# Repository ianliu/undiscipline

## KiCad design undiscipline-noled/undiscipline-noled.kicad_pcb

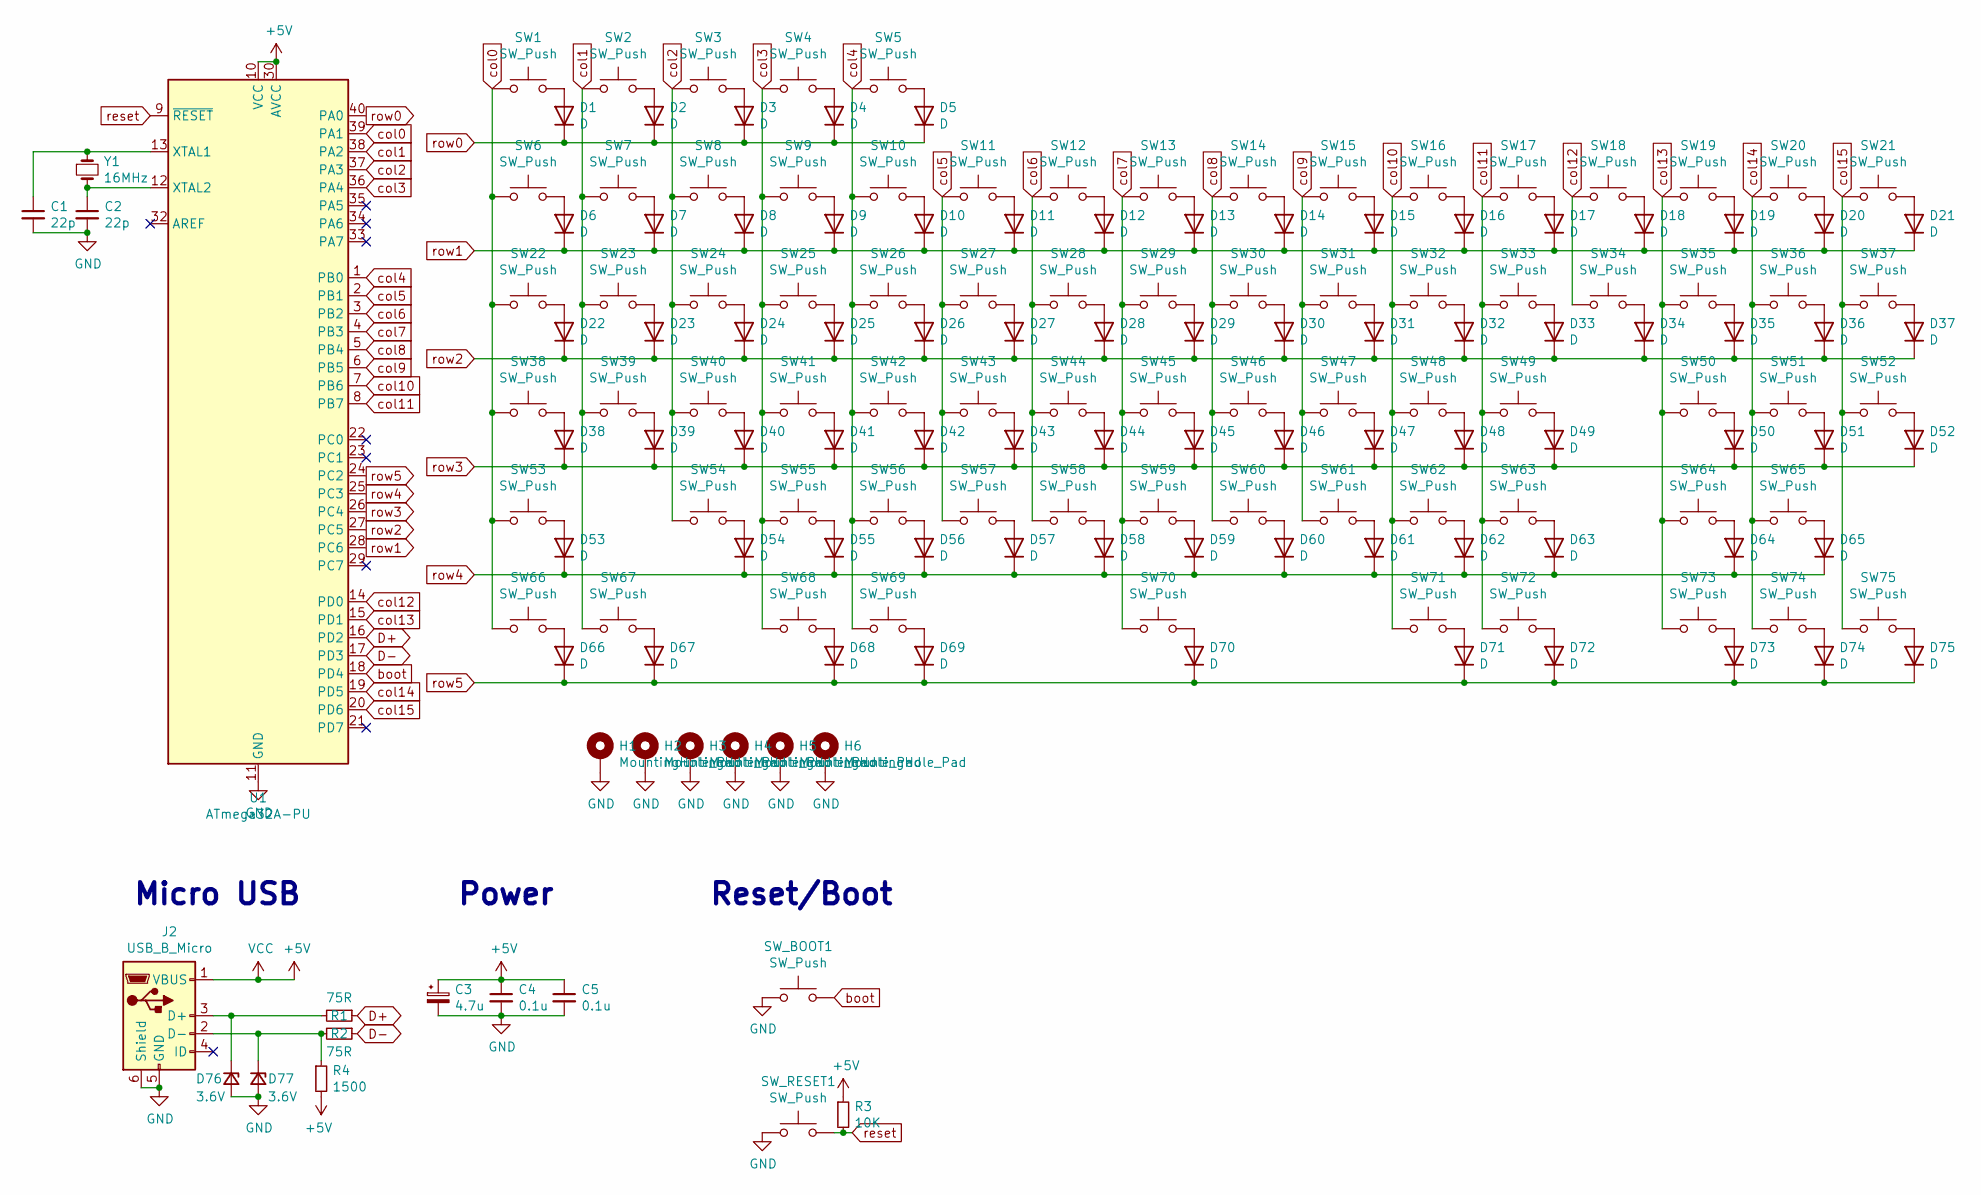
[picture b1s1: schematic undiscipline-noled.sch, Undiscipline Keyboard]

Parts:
C1, C2: 22p; C_Disc_D3.8mm_W2.6mm_P2.50mm
C3: 4.7u; CP_Radial_D5.0mm_P2.50mm
C4, C5: 0.1u; C_Disc_D4.3mm_W1.9mm_P5.00mm
D1, D2, D3, D4, D5, D6, D7, D8, D9, D10, D11, D12, D13, D14, D15, D16, D17, D18, D19, D20, D21, D22, D23, D24, D25, D26, D27, D28, D29, D30, D31, D32, D33, D34, D35, D36, D37, D38, D39, D40, D41, D42, D43, D44, D45, D46, D47, D48, D49, D50, D51, D52, D53, D54, D55, D56, D57, D58, D59, D60, D61, D62, D63, D64, D65, D66, D67, D68, D69, D70, D71, D72, D73, D74, D75: D; D_T-1_P5.08mm_Horizontal
D76, D77: 3.6V; D_T-1_P5.08mm_Horizontal
H1, H2, H3, H4, H5, H6: MountingHole_Pad; MountingHole_2.2mm_M2_DIN965_Pad_TopBottom
J2: USB_B_Micro; MicroUSB
R1, R2: 75R; R_Axial_DIN0204_L3.6mm_D1.6mm_P5.08mm_Horizontal
R3: 10K; R_Axial_DIN0204_L3.6mm_D1.6mm_P5.08mm_Horizontal
R4: 1500; R_Axial_DIN0204_L3.6mm_D1.6mm_P5.08mm_Horizontal
SW1, SW2, SW3, SW4, SW5, SW6, SW7, SW8, SW9, SW10, SW11, SW12, SW13, SW14, SW15, SW16, SW17, SW18, SW20, SW21, SW23, SW24, SW25, SW26, SW27, SW28, SW29, SW30, SW31, SW32, SW33, SW34, SW36, SW37, SW39, SW40, SW41, SW42, SW43, SW44, SW45, SW46, SW47, SW48, SW49, SW51, SW52, SW53, SW54, SW55, SW56, SW57, SW58, SW59, SW60, SW61, SW62, SW63, SW65, SW73, SW74, SW75: SW_Push; SW_Cherry_MX_1.00u_Plate
SW19: SW_Push; SW_Cherry_MX_2.00u_Plate
SW22, SW35: SW_Push; SW_Cherry_MX_1.50u_Plate
SW38: SW_Push; SW_Cherry_MX_1.75u_Plate
SW50: SW_Push; SW_Cherry_MX_2.25u_Plate
SW64: SW_Push; SW_Cherry_MX_2.75u_Plate
SW66, SW67, SW68, SW69, SW71, SW72: SW_Push; SW_Cherry_MX_1.25u_Plate
SW70: SW_Push; SW_Cherry_MX_6.25u_Plate
SW_BOOT1: SW_Push; SW_PUSH_6mm
SW_RESET1: SW_Push; SW_PUSH_6mm
U1: ATmega32A-PU; DIP-40_W15.24mm
Y1: 16MHz; Crystal_HC49-4H_Vertical

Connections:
+5V: C3.1, C4.1, C5.1, J2.1 (VBUS), R3.1, R4.2, U1.10 (VCC), U1.30 (AVCC)
D+: R1.1, U1.16 (PD2)
D-: R2.1, U1.17 (PD3)
GND: C1.2, C2.2, C3.2, C4.2, C5.2, D76.2 (A), D77.2 (A), H1.1, H2.1, H3.1, H4.1, H5.1, H6.1, J2.5 (GND), J2.6 (Shield), SW_BOOT1.1, SW_RESET1.1, U1.11 (GND), U1.31 (GND)
unnamed: C1.1, U1.13 (XTAL1), Y1.1
unnamed: C2.1, U1.12 (XTAL2), Y1.2
unnamed: D1.2 (A), SW1.2
unnamed: D2.2 (A), SW2.2
unnamed: D3.2 (A), SW3.2
unnamed: D4.2 (A), SW4.2
unnamed: D5.2 (A), SW5.2
unnamed: D6.2 (A), SW6.2
unnamed: D7.2 (A), SW7.2
unnamed: D8.2 (A), SW8.2
unnamed: D9.2 (A), SW9.2
unnamed: D10.2 (A), SW10.2
unnamed: D11.2 (A), SW11.2
unnamed: D12.2 (A), SW12.2
unnamed: D13.2 (A), SW13.2
unnamed: D14.2 (A), SW14.2
unnamed: D15.2 (A), SW15.2
unnamed: D16.2 (A), SW16.2
unnamed: D17.2 (A), SW17.2
unnamed: D18.2 (A), SW18.2
unnamed: D19.2 (A), SW19.2
unnamed: D20.2 (A), SW20.2
unnamed: D21.2 (A), SW21.2
unnamed: D22.2 (A), SW22.2
unnamed: D23.2 (A), SW23.2
unnamed: D24.2 (A), SW24.2
unnamed: D25.2 (A), SW25.2
unnamed: D26.2 (A), SW26.2
unnamed: D27.2 (A), SW27.2
unnamed: D28.2 (A), SW28.2
unnamed: D29.2 (A), SW29.2
unnamed: D30.2 (A), SW30.2
unnamed: D31.2 (A), SW31.2
unnamed: D32.2 (A), SW32.2
unnamed: D33.2 (A), SW33.2
unnamed: D34.2 (A), SW34.2
unnamed: D35.2 (A), SW35.2
unnamed: D36.2 (A), SW36.2
unnamed: D37.2 (A), SW37.2
unnamed: D38.2 (A), SW38.2
unnamed: D39.2 (A), SW39.2
unnamed: D40.2 (A), SW40.2
unnamed: D41.2 (A), SW41.2
unnamed: D42.2 (A), SW42.2
unnamed: D43.2 (A), SW43.2
unnamed: D44.2 (A), SW44.2
unnamed: D45.2 (A), SW45.2
unnamed: D46.2 (A), SW46.2
unnamed: D47.2 (A), SW47.2
unnamed: D48.2 (A), SW48.2
unnamed: D49.2 (A), SW49.2
unnamed: D50.2 (A), SW50.2
unnamed: D51.2 (A), SW51.2
unnamed: D52.2 (A), SW52.2
unnamed: D53.2 (A), SW53.2
unnamed: D54.2 (A), SW54.2
unnamed: D55.2 (A), SW55.2
unnamed: D56.2 (A), SW56.2
unnamed: D57.2 (A), SW57.2
unnamed: D58.2 (A), SW58.2
unnamed: D59.2 (A), SW59.2
unnamed: D60.2 (A), SW60.2
unnamed: D61.2 (A), SW61.2
unnamed: D62.2 (A), SW62.2
unnamed: D63.2 (A), SW63.2
unnamed: D64.2 (A), SW64.2
unnamed: D65.2 (A), SW65.2
unnamed: D66.2 (A), SW66.2
unnamed: D67.2 (A), SW67.2
unnamed: D68.2 (A), SW68.2
unnamed: D69.2 (A), SW69.2
unnamed: D70.2 (A), SW70.2
unnamed: D71.2 (A), SW71.2
unnamed: D72.2 (A), SW72.2
unnamed: D73.2 (A), SW73.2
unnamed: D74.2 (A), SW74.2
unnamed: D75.2 (A), SW75.2
unnamed: D76.1 (K), J2.3 (D+), R1.2
unnamed: D77.1 (K), J2.2 (D-), R2.2, R4.1
boot: SW_BOOT1.2, U1.18 (PD4)
col0: SW1.1, SW6.1, SW22.1, SW38.1, SW53.1, SW66.1, U1.39 (PA1)
col1: SW2.1, SW7.1, SW23.1, SW39.1, SW67.1, U1.38 (PA2)
col2: SW3.1, SW8.1, SW24.1, SW40.1, SW54.1, U1.37 (PA3)
col3: SW4.1, SW9.1, SW25.1, SW41.1, SW55.1, SW68.1, U1.36 (PA4)
col4: SW5.1, SW10.1, SW26.1, SW42.1, SW56.1, SW69.1, U1.1 (PB0)
col5: SW11.1, SW27.1, SW43.1, SW57.1, U1.2 (PB1)
col6: SW12.1, SW28.1, SW44.1, SW58.1, U1.3 (PB2)
col7: SW13.1, SW29.1, SW45.1, SW59.1, SW70.1, U1.4 (PB3)
col8: SW14.1, SW30.1, SW46.1, SW60.1, U1.5 (PB4)
col9: SW15.1, SW31.1, SW47.1, SW61.1, U1.6 (PB5)
col10: SW16.1, SW32.1, SW48.1, SW62.1, SW71.1, U1.7 (PB6)
col11: SW17.1, SW33.1, SW49.1, SW63.1, SW72.1, U1.8 (PB7)
col12: SW18.1, SW34.1, U1.14 (PD0)
col13: SW19.1, SW35.1, SW50.1, SW64.1, SW73.1, U1.15 (PD1)
col14: SW20.1, SW36.1, SW51.1, SW65.1, SW74.1, U1.19 (PD5)
col15: SW21.1, SW37.1, SW52.1, SW75.1, U1.20 (PD6)
reset: R3.2, SW_RESET1.2, U1.9 (~RESET)
row0: D1.1 (K), D2.1 (K), D3.1 (K), D4.1 (K), D5.1 (K), U1.40 (PA0)
row1: D6.1 (K), D7.1 (K), D8.1 (K), D9.1 (K), D10.1 (K), D11.1 (K), D12.1 (K), D13.1 (K), D14.1 (K), D15.1 (K), D16.1 (K), D17.1 (K), D18.1 (K), D19.1 (K), D20.1 (K), D21.1 (K), U1.28 (PC6)
row2: D22.1 (K), D23.1 (K), D24.1 (K), D25.1 (K), D26.1 (K), D27.1 (K), D28.1 (K), D29.1 (K), D30.1 (K), D31.1 (K), D32.1 (K), D33.1 (K), D34.1 (K), D35.1 (K), D36.1 (K), D37.1 (K), U1.27 (PC5)
row3: D38.1 (K), D39.1 (K), D40.1 (K), D41.1 (K), D42.1 (K), D43.1 (K), D44.1 (K), D45.1 (K), D46.1 (K), D47.1 (K), D48.1 (K), D49.1 (K), D50.1 (K), D51.1 (K), D52.1 (K), U1.26 (PC4)
row4: D53.1 (K), D54.1 (K), D55.1 (K), D56.1 (K), D57.1 (K), D58.1 (K), D59.1 (K), D60.1 (K), D61.1 (K), D62.1 (K), D63.1 (K), D64.1 (K), D65.1 (K), U1.25 (PC3)
row5: D66.1 (K), D67.1 (K), D68.1 (K), D69.1 (K), D70.1 (K), D71.1 (K), D72.1 (K), D73.1 (K), D74.1 (K), D75.1 (K), U1.24 (PC2)

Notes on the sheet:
Micro USB
Power
Reset/Boot

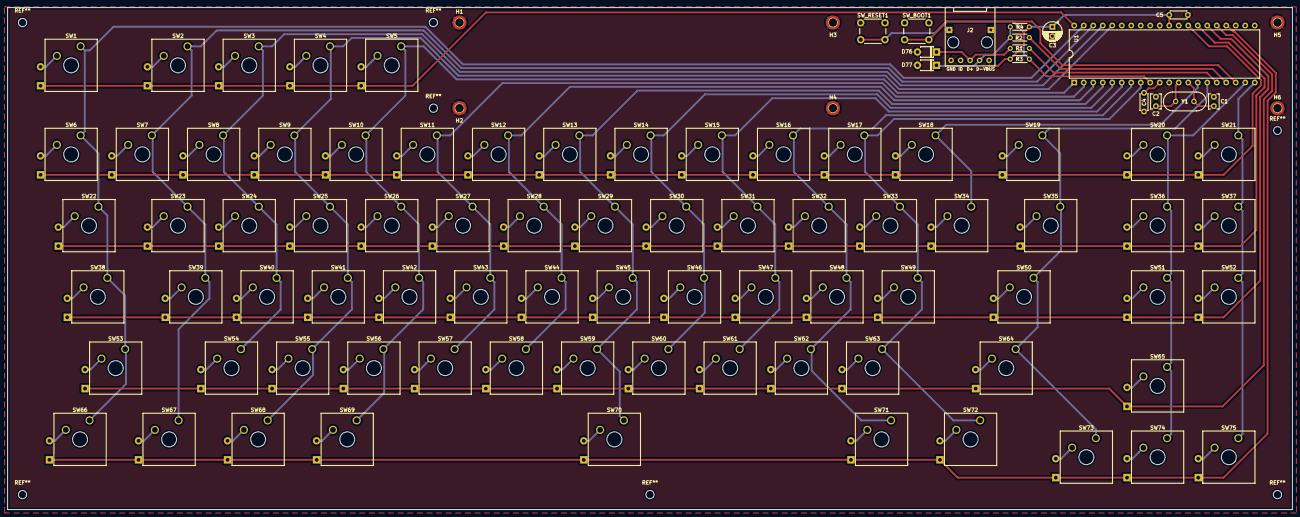
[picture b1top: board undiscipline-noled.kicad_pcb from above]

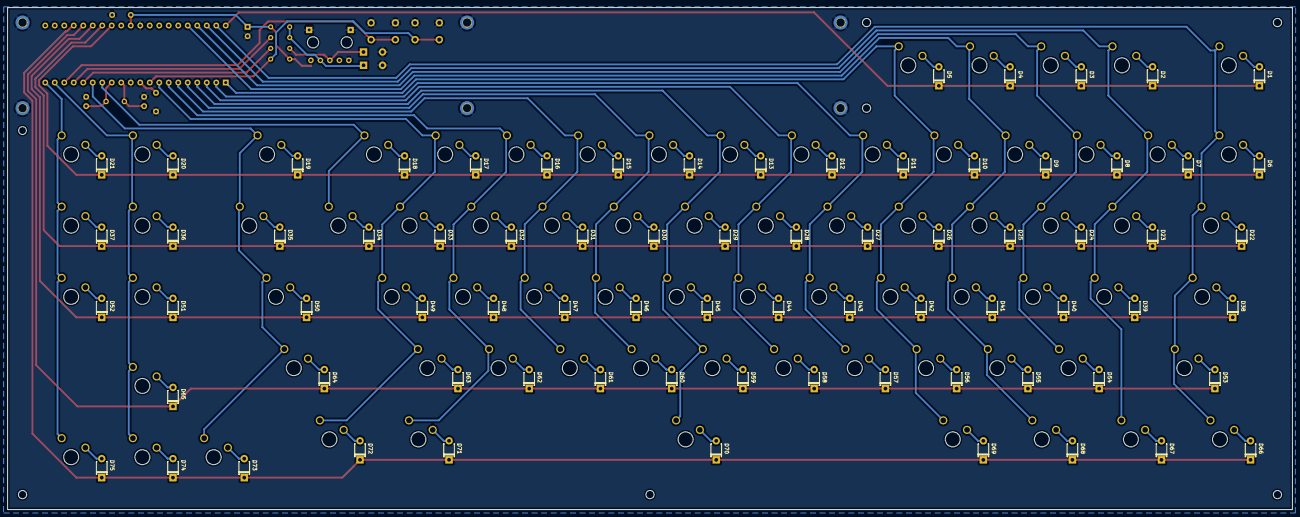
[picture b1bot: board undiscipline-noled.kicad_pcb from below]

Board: 4 copper layers, 343.6 x 134.2 mm, 172 parts (75 on the bottom side), 107 nets.

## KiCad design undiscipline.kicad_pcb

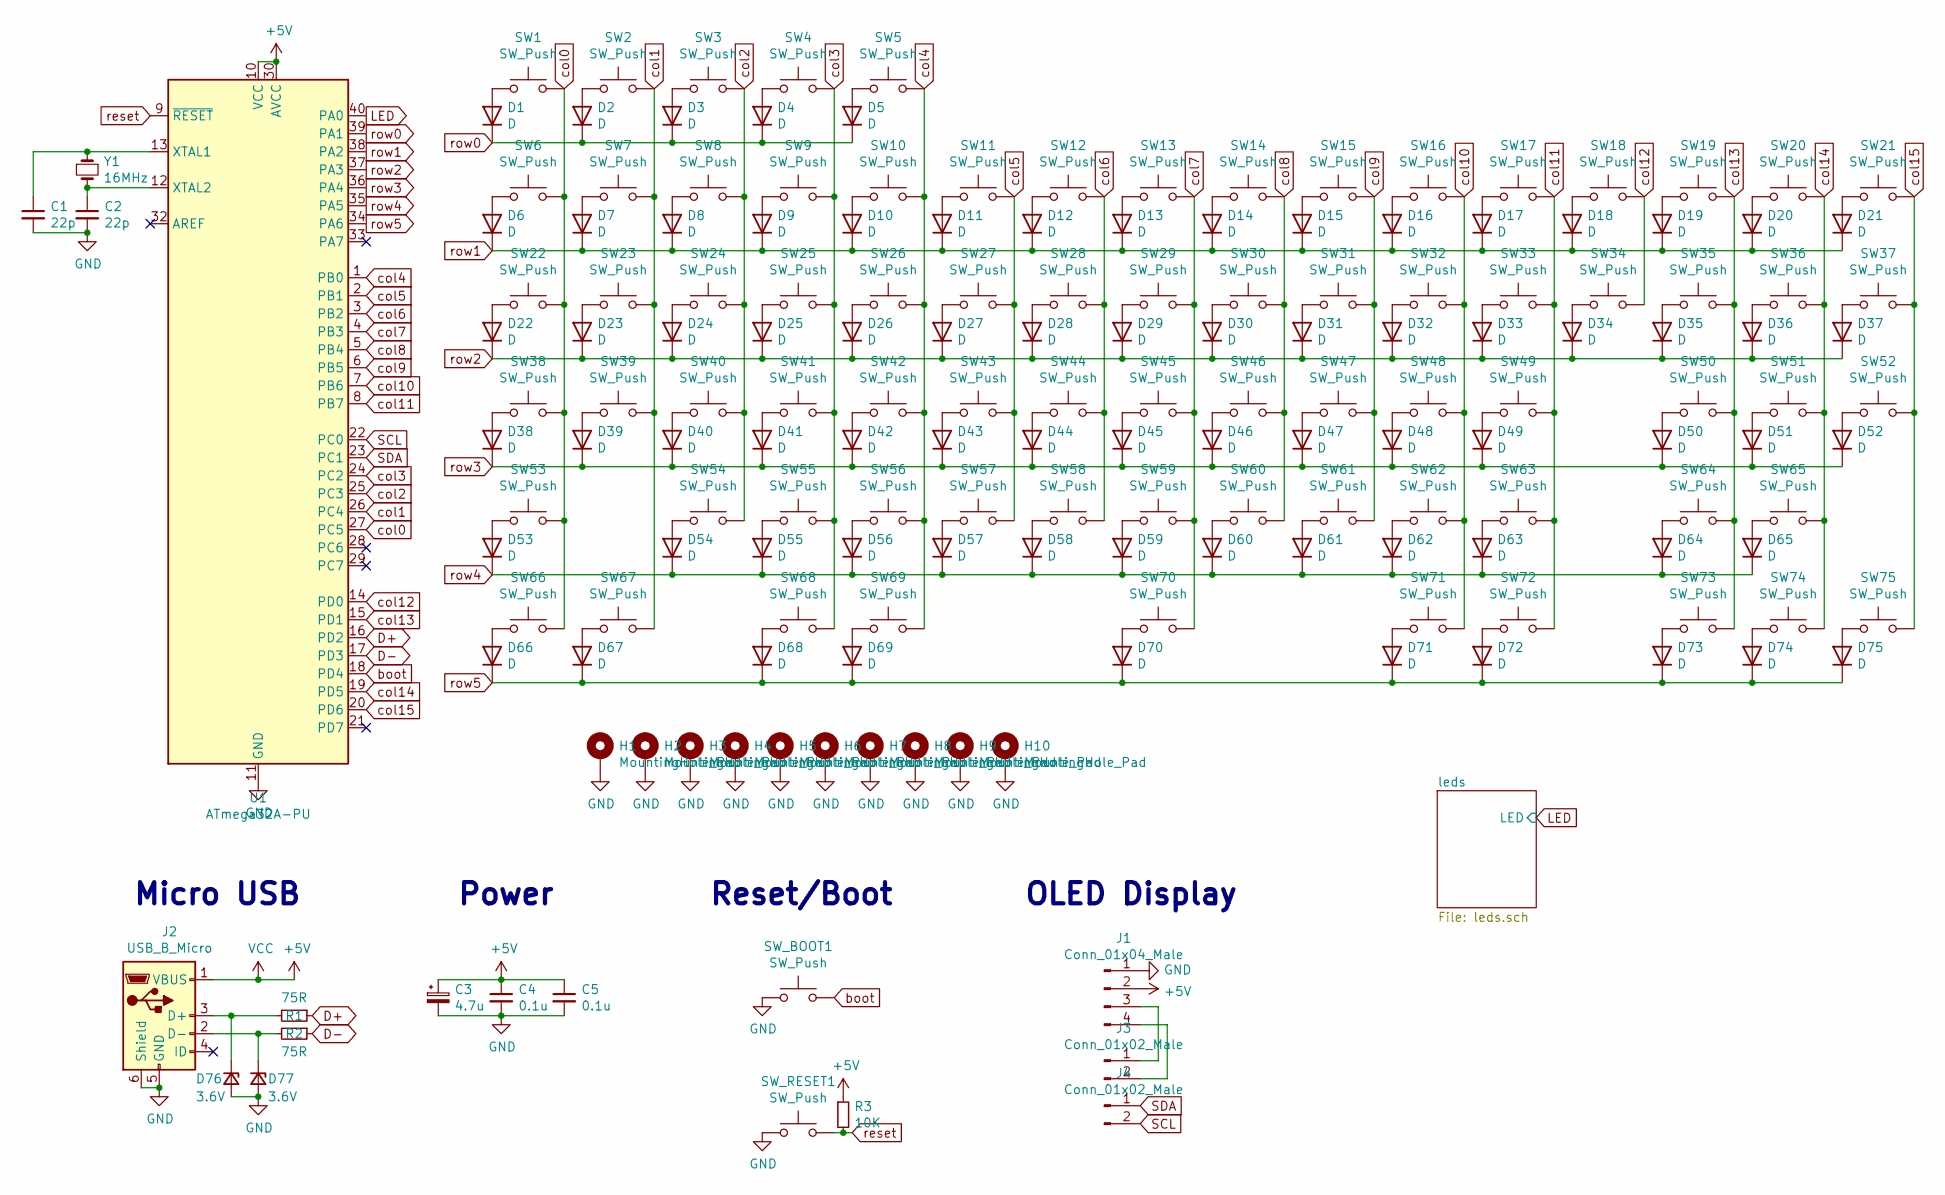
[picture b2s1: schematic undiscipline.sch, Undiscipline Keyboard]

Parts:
C1, C2: 22p; C_Disc_D3.8mm_W2.6mm_P2.50mm
C3: 4.7u; CP_Radial_D5.0mm_P2.50mm
C4, C5: 0.1u; C_Disc_D4.3mm_W1.9mm_P5.00mm
D1, D2, D3, D4, D5, D6, D7, D8, D9, D10, D11, D12, D13, D14, D15, D16, D17, D18, D19, D20, D21, D22, D23, D24, D25, D26, D27, D28, D29, D30, D31, D32, D33, D34, D35, D36, D37, D38, D39, D40, D41, D42, D43, D44, D45, D46, D47, D48, D49, D50, D51, D52, D53, D54, D55, D56, D57, D58, D59, D60, D61, D62, D63, D64, D65, D66, D67, D68, D69, D70, D71, D72, D73, D74, D75: D; D_T-1_P5.08mm_Horizontal
D76, D77: 3.6V; D_T-1_P5.08mm_Horizontal
H1, H2, H3, H4, H5, H6, H7, H8, H9, H10: MountingHole_Pad; MountingHole_2.2mm_M2_DIN965_Pad_TopBottom
J1: Conn_01x04_Male; OLED128x64
J2: USB_B_Micro; MicroUSB
J3, J4: Conn_01x02_Male; PinHeader_1x02_P2.54mm_Horizontal
R1, R2: 75R; R_Axial_DIN0204_L3.6mm_D1.6mm_P5.08mm_Horizontal
R3: 10K; R_Axial_DIN0204_L3.6mm_D1.6mm_P5.08mm_Horizontal
SW1, SW2, SW3, SW4, SW5, SW6, SW7, SW8, SW9, SW10, SW11, SW12, SW13, SW14, SW15, SW16, SW17, SW18, SW19, SW20, SW21, SW22, SW23, SW24, SW25, SW26, SW27, SW28, SW29, SW30, SW31, SW32, SW33, SW34, SW35, SW36, SW37, SW38, SW39, SW40, SW41, SW42, SW43, SW44, SW45, SW46, SW47, SW48, SW49, SW50, SW51, SW52, SW53, SW54, SW55, SW56, SW57, SW58, SW59, SW60, SW61, SW62, SW63, SW64, SW65, SW66, SW67, SW68, SW69, SW70, SW71, SW72, SW73, SW74, SW75: SW_Push; CherryMX_Kailh_Socket
SW_BOOT1: SW_Push; SW_PUSH_6mm
SW_RESET1: SW_Push; SW_PUSH_6mm
U1: ATmega32A-PU; DIP-40_W15.24mm
Y1: 16MHz; Crystal_HC49-4H_Vertical

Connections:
+5V: C3.1, C4.1, C5.1, J1.2, J2.1 (VBUS), R3.1, U1.10 (VCC), U1.30 (AVCC); also elsewhere on the board
D+: R1.1, U1.16 (PD2)
D-: R2.1, U1.17 (PD3)
GND: C1.2, C2.2, C3.2, C4.2, C5.2, D76.2 (A), D77.2 (A), H1.1, H2.1, H3.1, H4.1, H5.1, H6.1, H7.1, H8.1, H9.1, H10.1, J1.1, J2.5 (GND), J2.6 (Shield), SW_BOOT1.1, SW_RESET1.1, U1.11 (GND), U1.31 (GND); also elsewhere on the board
LED: U1.40 (PA0); also elsewhere on the board
unnamed: C1.1, U1.13 (XTAL1), Y1.1
unnamed: C2.1, U1.12 (XTAL2), Y1.2
unnamed: D1.2 (A), SW1.1
unnamed: D2.2 (A), SW2.1
unnamed: D3.2 (A), SW3.1
unnamed: D4.2 (A), SW4.1
unnamed: D5.2 (A), SW5.1
unnamed: D6.2 (A), SW6.1
unnamed: D7.2 (A), SW7.1
unnamed: D8.2 (A), SW8.1
unnamed: D9.2 (A), SW9.1
unnamed: D10.2 (A), SW10.1
unnamed: D11.2 (A), SW11.1
unnamed: D12.2 (A), SW12.1
unnamed: D13.2 (A), SW13.1
unnamed: D14.2 (A), SW14.1
unnamed: D15.2 (A), SW15.1
unnamed: D16.2 (A), SW16.1
unnamed: D17.2 (A), SW17.1
unnamed: D18.2 (A), SW18.1
unnamed: D19.2 (A), SW19.1
unnamed: D20.2 (A), SW20.1
unnamed: D21.2 (A), SW21.1
unnamed: D22.2 (A), SW22.1
unnamed: D23.2 (A), SW23.1
unnamed: D24.2 (A), SW24.1
unnamed: D25.2 (A), SW25.1
unnamed: D26.2 (A), SW26.1
unnamed: D27.2 (A), SW27.1
unnamed: D28.2 (A), SW28.1
unnamed: D29.2 (A), SW29.1
unnamed: D30.2 (A), SW30.1
unnamed: D31.2 (A), SW31.1
unnamed: D32.2 (A), SW32.1
unnamed: D33.2 (A), SW33.1
unnamed: D34.2 (A), SW34.1
unnamed: D35.2 (A), SW35.1
unnamed: D36.2 (A), SW36.1
unnamed: D37.2 (A), SW37.1
unnamed: D38.2 (A), SW38.1
unnamed: D39.2 (A), SW39.1
unnamed: D40.2 (A), SW40.1
unnamed: D41.2 (A), SW41.1
unnamed: D42.2 (A), SW42.1
unnamed: D43.2 (A), SW43.1
unnamed: D44.2 (A), SW44.1
unnamed: D45.2 (A), SW45.1
unnamed: D46.2 (A), SW46.1
unnamed: D47.2 (A), SW47.1
unnamed: D48.2 (A), SW48.1
unnamed: D49.2 (A), SW49.1
unnamed: D50.2 (A), SW50.1
unnamed: D51.2 (A), SW51.1
unnamed: D52.2 (A), SW52.1
unnamed: D53.2 (A), SW53.1
unnamed: D54.2 (A), SW54.1
unnamed: D55.2 (A), SW55.1
unnamed: D56.2 (A), SW56.1
unnamed: D57.2 (A), SW57.1
unnamed: D58.2 (A), SW58.1
unnamed: D59.2 (A), SW59.1
unnamed: D60.2 (A), SW60.1
unnamed: D61.2 (A), SW61.1
unnamed: D62.2 (A), SW62.1
unnamed: D63.2 (A), SW63.1
unnamed: D64.2 (A), SW64.1
unnamed: D65.2 (A), SW65.1
unnamed: D66.2 (A), SW66.1
unnamed: D67.2 (A), SW67.1
unnamed: D68.2 (A), SW68.1
unnamed: D69.2 (A), SW69.1
unnamed: D70.2 (A), SW70.1
unnamed: D71.2 (A), SW71.1
unnamed: D72.2 (A), SW72.1
unnamed: D73.2 (A), SW73.1
unnamed: D74.2 (A), SW74.1
unnamed: D75.2 (A), SW75.1
unnamed: D76.1 (K), J2.3 (D+), R1.2
unnamed 83: D77.1 (K), J2.2 (D-), R2.2; also elsewhere on the board
unnamed: J1.3, J3.1
unnamed: J1.4, J3.2
SCL: J4.2, U1.22 (PC0)
SDA: J4.1, U1.23 (PC1)
boot: SW_BOOT1.2, U1.18 (PD4)
col0: SW1.2, SW6.2, SW22.2, SW38.2, SW53.2, SW66.2, U1.27 (PC5)
col1: SW2.2, SW7.2, SW23.2, SW39.2, SW67.2, U1.26 (PC4)
col2: SW3.2, SW8.2, SW24.2, SW40.2, SW54.2, U1.25 (PC3)
col3: SW4.2, SW9.2, SW25.2, SW41.2, SW55.2, SW68.2, U1.24 (PC2)
col4: SW5.2, SW10.2, SW26.2, SW42.2, SW56.2, SW69.2, U1.1 (PB0)
col5: SW11.2, SW27.2, SW43.2, SW57.2, U1.2 (PB1)
col6: SW12.2, SW28.2, SW44.2, SW58.2, U1.3 (PB2)
col7: SW13.2, SW29.2, SW45.2, SW59.2, SW70.2, U1.4 (PB3)
col8: SW14.2, SW30.2, SW46.2, SW60.2, U1.5 (PB4)
col9: SW15.2, SW31.2, SW47.2, SW61.2, U1.6 (PB5)
col10: SW16.2, SW32.2, SW48.2, SW62.2, SW71.2, U1.7 (PB6)
col11: SW17.2, SW33.2, SW49.2, SW63.2, SW72.2, U1.8 (PB7)
col12: SW18.2, SW34.2, U1.14 (PD0)
col13: SW19.2, SW35.2, SW50.2, SW64.2, SW73.2, U1.15 (PD1)
col14: SW20.2, SW36.2, SW51.2, SW65.2, SW74.2, U1.19 (PD5)
col15: SW21.2, SW37.2, SW52.2, SW75.2, U1.20 (PD6)
reset: R3.2, SW_RESET1.2, U1.9 (~RESET)
row0: D1.1 (K), D2.1 (K), D3.1 (K), D4.1 (K), D5.1 (K), U1.39 (PA1)
row1: D6.1 (K), D7.1 (K), D8.1 (K), D9.1 (K), D10.1 (K), D11.1 (K), D12.1 (K), D13.1 (K), D14.1 (K), D15.1 (K), D16.1 (K), D17.1 (K), D18.1 (K), D19.1 (K), D20.1 (K), D21.1 (K), U1.38 (PA2)
row2: D22.1 (K), D23.1 (K), D24.1 (K), D25.1 (K), D26.1 (K), D27.1 (K), D28.1 (K), D29.1 (K), D30.1 (K), D31.1 (K), D32.1 (K), D33.1 (K), D34.1 (K), D35.1 (K), D36.1 (K), D37.1 (K), U1.37 (PA3)
row3: D38.1 (K), D39.1 (K), D40.1 (K), D41.1 (K), D42.1 (K), D43.1 (K), D44.1 (K), D45.1 (K), D46.1 (K), D47.1 (K), D48.1 (K), D49.1 (K), D50.1 (K), D51.1 (K), D52.1 (K), U1.36 (PA4)
row4: D53.1 (K), D54.1 (K), D55.1 (K), D56.1 (K), D57.1 (K), D58.1 (K), D59.1 (K), D60.1 (K), D61.1 (K), D62.1 (K), D63.1 (K), D64.1 (K), D65.1 (K), U1.35 (PA5)
row5: D66.1 (K), D67.1 (K), D68.1 (K), D69.1 (K), D70.1 (K), D71.1 (K), D72.1 (K), D73.1 (K), D74.1 (K), D75.1 (K), U1.34 (PA6)

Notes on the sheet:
Micro USB
Power
Reset/Boot
OLED Display

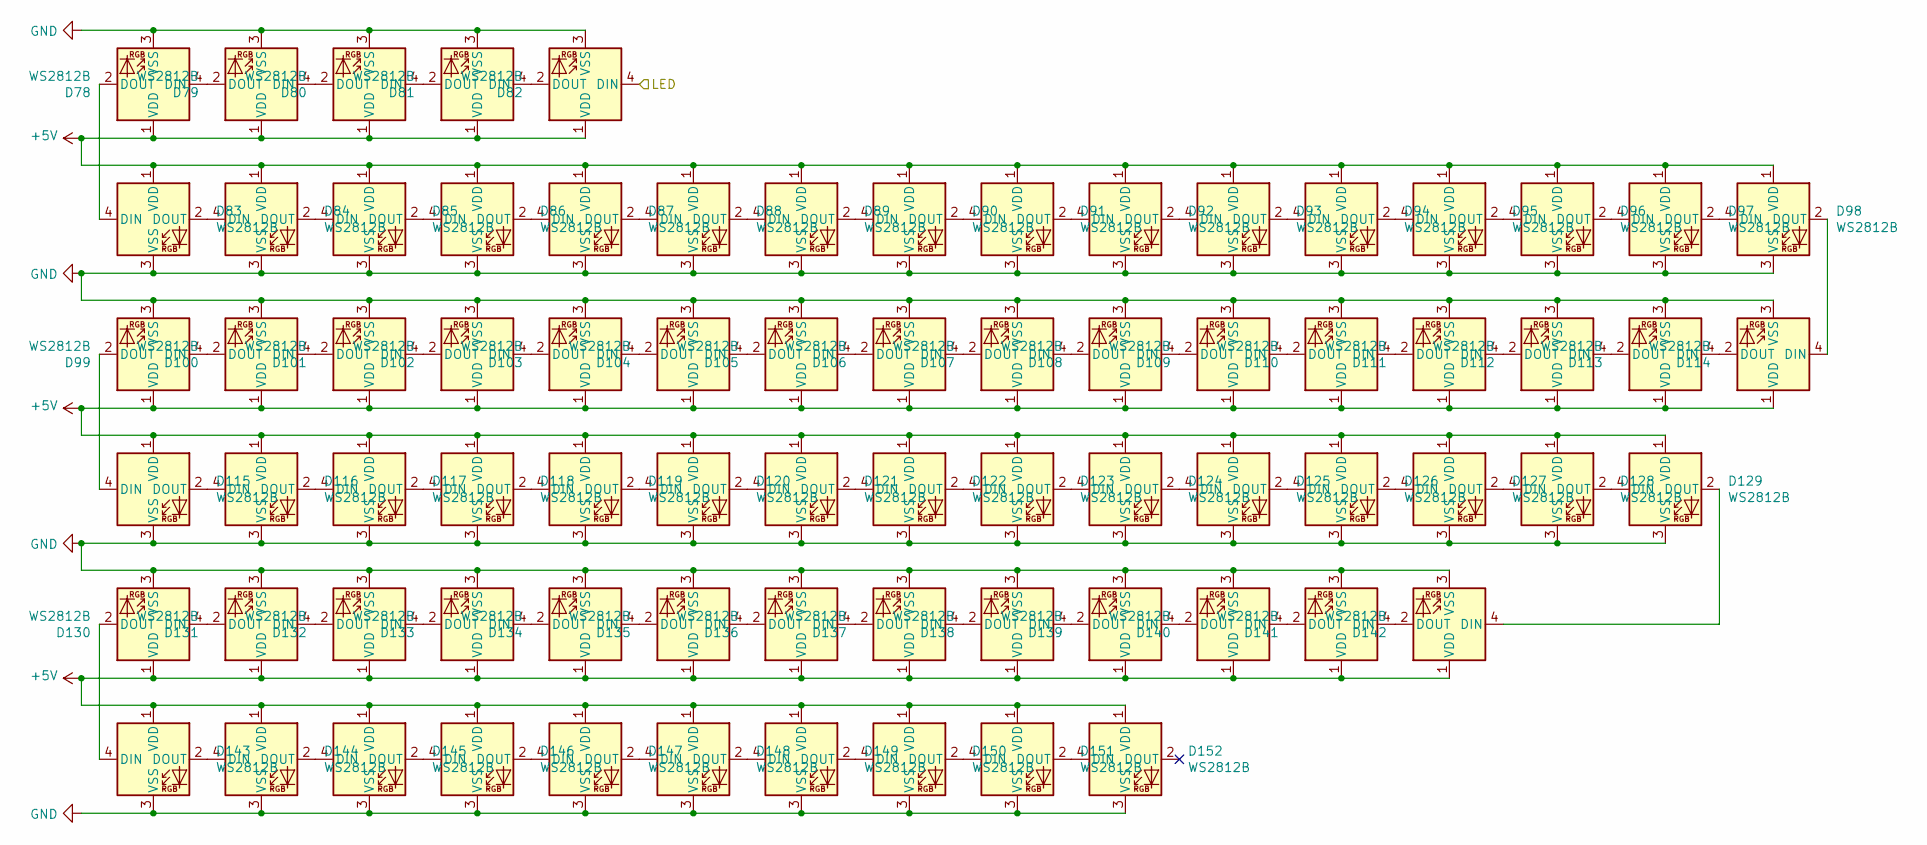
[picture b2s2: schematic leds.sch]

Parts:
D78, D79, D80, D81, D82, D83, D84, D85, D86, D87, D88, D89, D90, D91, D92, D93, D94, D95, D96, D97, D98, D99, D100, D101, D102, D103, D104, D105, D106, D107, D108, D109, D110, D111, D112, D113, D114, D115, D116, D117, D118, D119, D120, D121, D122, D123, D124, D125, D126, D127, D128, D129, D130, D131, D132, D133, D134, D135, D136, D137, D138, D139, D140, D141, D142, D143, D144, D145, D146, D147, D148, D149, D150, D151, D152: WS2812B; LED_WS2812B_PLCC4_5.0x5.0mm_P3.2mm

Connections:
+5V: D78.1 (VDD), D79.1 (VDD), D80.1 (VDD), D81.1 (VDD), D82.1 (VDD), D83.1 (VDD), D84.1 (VDD), D85.1 (VDD), D86.1 (VDD), D87.1 (VDD), D88.1 (VDD), D89.1 (VDD), D90.1 (VDD), D91.1 (VDD), D92.1 (VDD), D93.1 (VDD), D94.1 (VDD), D95.1 (VDD), D96.1 (VDD), D97.1 (VDD), D98.1 (VDD), D99.1 (VDD), D100.1 (VDD), D101.1 (VDD), D102.1 (VDD), D103.1 (VDD), D104.1 (VDD), D105.1 (VDD), D106.1 (VDD), D107.1 (VDD), D108.1 (VDD), D109.1 (VDD), D110.1 (VDD), D111.1 (VDD), D112.1 (VDD), D113.1 (VDD), D114.1 (VDD), D115.1 (VDD), D116.1 (VDD), D117.1 (VDD), D118.1 (VDD), D119.1 (VDD), D120.1 (VDD), D121.1 (VDD), D122.1 (VDD), D123.1 (VDD), D124.1 (VDD), D125.1 (VDD), D126.1 (VDD), D127.1 (VDD), D128.1 (VDD), D129.1 (VDD), D130.1 (VDD), D131.1 (VDD), D132.1 (VDD), D133.1 (VDD), D134.1 (VDD), D135.1 (VDD), D136.1 (VDD), D137.1 (VDD), D138.1 (VDD), D139.1 (VDD), D140.1 (VDD), D141.1 (VDD), D142.1 (VDD), D143.1 (VDD), D144.1 (VDD), D145.1 (VDD), D146.1 (VDD), D147.1 (VDD), D148.1 (VDD), D149.1 (VDD), D150.1 (VDD), D151.1 (VDD), D152.1 (VDD); also elsewhere on the board
GND: D78.3 (VSS), D79.3 (VSS), D80.3 (VSS), D81.3 (VSS), D82.3 (VSS), D83.3 (VSS), D84.3 (VSS), D85.3 (VSS), D86.3 (VSS), D87.3 (VSS), D88.3 (VSS), D89.3 (VSS), D90.3 (VSS), D91.3 (VSS), D92.3 (VSS), D93.3 (VSS), D94.3 (VSS), D95.3 (VSS), D96.3 (VSS), D97.3 (VSS), D98.3 (VSS), D99.3 (VSS), D100.3 (VSS), D101.3 (VSS), D102.3 (VSS), D103.3 (VSS), D104.3 (VSS), D105.3 (VSS), D106.3 (VSS), D107.3 (VSS), D108.3 (VSS), D109.3 (VSS), D110.3 (VSS), D111.3 (VSS), D112.3 (VSS), D113.3 (VSS), D114.3 (VSS), D115.3 (VSS), D116.3 (VSS), D117.3 (VSS), D118.3 (VSS), D119.3 (VSS), D120.3 (VSS), D121.3 (VSS), D122.3 (VSS), D123.3 (VSS), D124.3 (VSS), D125.3 (VSS), D126.3 (VSS), D127.3 (VSS), D128.3 (VSS), D129.3 (VSS), D130.3 (VSS), D131.3 (VSS), D132.3 (VSS), D133.3 (VSS), D134.3 (VSS), D135.3 (VSS), D136.3 (VSS), D137.3 (VSS), D138.3 (VSS), D139.3 (VSS), D140.3 (VSS), D141.3 (VSS), D142.3 (VSS), D143.3 (VSS), D144.3 (VSS), D145.3 (VSS), D146.3 (VSS), D147.3 (VSS), D148.3 (VSS), D149.3 (VSS), D150.3 (VSS), D151.3 (VSS), D152.3 (VSS); also elsewhere on the board
LED: D82.4 (DIN); also elsewhere on the board
unnamed: D78.2 (DOUT), D83.4 (DIN)
unnamed: D78.4 (DIN), D79.2 (DOUT)
unnamed: D79.4 (DIN), D80.2 (DOUT)
unnamed: D80.4 (DIN), D81.2 (DOUT)
unnamed: D81.4 (DIN), D82.2 (DOUT)
unnamed: D83.2 (DOUT), D84.4 (DIN)
unnamed: D84.2 (DOUT), D85.4 (DIN)
unnamed: D85.2 (DOUT), D86.4 (DIN)
unnamed: D86.2 (DOUT), D87.4 (DIN)
unnamed: D87.2 (DOUT), D88.4 (DIN)
unnamed: D88.2 (DOUT), D89.4 (DIN)
unnamed: D89.2 (DOUT), D90.4 (DIN)
unnamed: D90.2 (DOUT), D91.4 (DIN)
unnamed: D91.2 (DOUT), D92.4 (DIN)
unnamed: D92.2 (DOUT), D93.4 (DIN)
unnamed: D93.2 (DOUT), D94.4 (DIN)
unnamed: D94.2 (DOUT), D95.4 (DIN)
unnamed: D95.2 (DOUT), D96.4 (DIN)
unnamed: D96.2 (DOUT), D97.4 (DIN)
unnamed: D97.2 (DOUT), D98.4 (DIN)
unnamed: D99.4 (DIN), D100.2 (DOUT)
unnamed: D100.4 (DIN), D101.2 (DOUT)
unnamed: D101.4 (DIN), D102.2 (DOUT)
unnamed: D102.4 (DIN), D103.2 (DOUT)
unnamed: D103.4 (DIN), D104.2 (DOUT)
unnamed: D104.4 (DIN), D105.2 (DOUT)
unnamed: D105.4 (DIN), D106.2 (DOUT)
unnamed: D106.4 (DIN), D107.2 (DOUT)
unnamed: D107.4 (DIN), D108.2 (DOUT)
unnamed: D108.4 (DIN), D109.2 (DOUT)
unnamed: D109.4 (DIN), D110.2 (DOUT)
unnamed: D110.4 (DIN), D111.2 (DOUT)
unnamed: D111.4 (DIN), D112.2 (DOUT)
unnamed: D112.4 (DIN), D113.2 (DOUT)
unnamed: D113.4 (DIN), D114.2 (DOUT)
unnamed: D98.2 (DOUT), D114.4 (DIN)
unnamed: D115.2 (DOUT), D116.4 (DIN)
unnamed: D99.2 (DOUT), D115.4 (DIN)
unnamed: D116.2 (DOUT), D117.4 (DIN)
unnamed: D117.2 (DOUT), D118.4 (DIN)
unnamed: D118.2 (DOUT), D119.4 (DIN)
unnamed: D119.2 (DOUT), D120.4 (DIN)
unnamed: D120.2 (DOUT), D121.4 (DIN)
unnamed: D121.2 (DOUT), D122.4 (DIN)
unnamed: D122.2 (DOUT), D123.4 (DIN)
unnamed: D123.2 (DOUT), D124.4 (DIN)
unnamed: D124.2 (DOUT), D125.4 (DIN)
unnamed: D125.2 (DOUT), D126.4 (DIN)
unnamed: D126.2 (DOUT), D127.4 (DIN)
unnamed: D127.2 (DOUT), D128.4 (DIN)
unnamed: D128.2 (DOUT), D129.4 (DIN)
unnamed: D129.2 (DOUT), D142.4 (DIN)
unnamed: D130.2 (DOUT), D143.4 (DIN)
unnamed: D130.4 (DIN), D131.2 (DOUT)
unnamed: D131.4 (DIN), D132.2 (DOUT)
unnamed: D132.4 (DIN), D133.2 (DOUT)
unnamed: D133.4 (DIN), D134.2 (DOUT)
unnamed: D134.4 (DIN), D135.2 (DOUT)
unnamed: D135.4 (DIN), D136.2 (DOUT)
unnamed: D136.4 (DIN), D137.2 (DOUT)
unnamed: D137.4 (DIN), D138.2 (DOUT)
unnamed: D138.4 (DIN), D139.2 (DOUT)
unnamed: D139.4 (DIN), D140.2 (DOUT)
unnamed: D140.4 (DIN), D141.2 (DOUT)
unnamed: D141.4 (DIN), D142.2 (DOUT)
unnamed: D143.2 (DOUT), D144.4 (DIN)
unnamed: D144.2 (DOUT), D145.4 (DIN)
unnamed: D145.2 (DOUT), D146.4 (DIN)
unnamed: D146.2 (DOUT), D147.4 (DIN)
unnamed: D147.2 (DOUT), D148.4 (DIN)
unnamed: D148.2 (DOUT), D149.4 (DIN)
unnamed: D149.2 (DOUT), D150.4 (DIN)
unnamed: D150.2 (DOUT), D151.4 (DIN)
unnamed: D151.2 (DOUT), D152.4 (DIN)

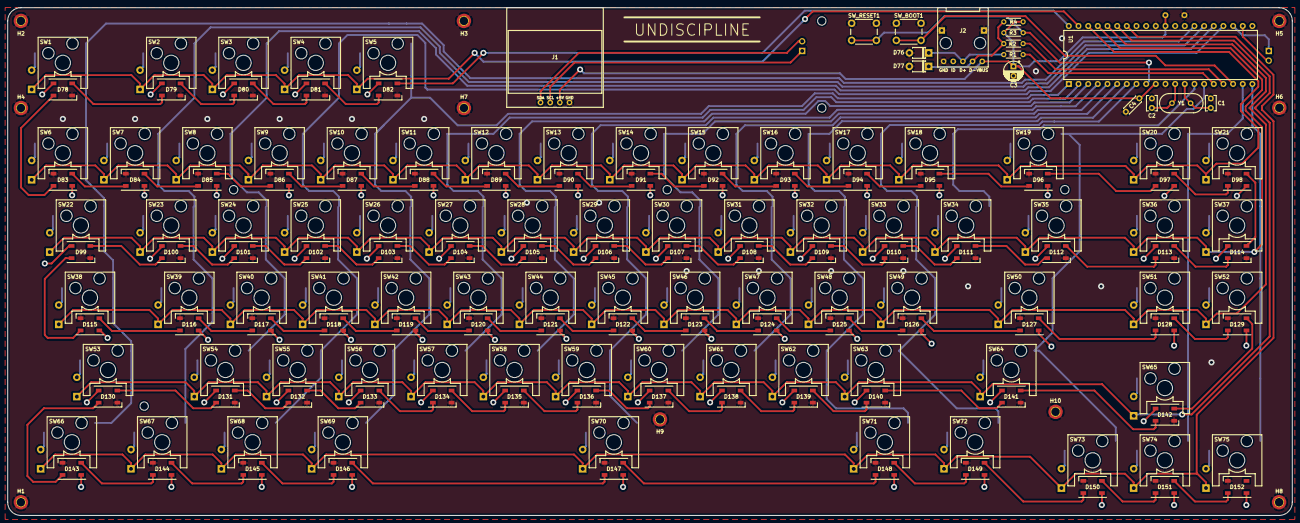
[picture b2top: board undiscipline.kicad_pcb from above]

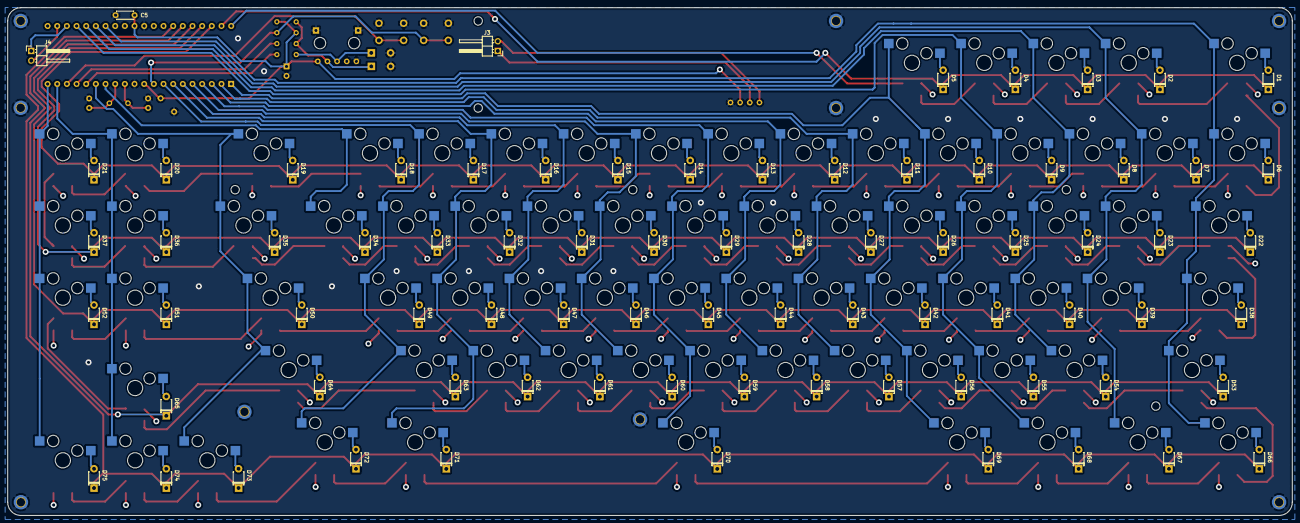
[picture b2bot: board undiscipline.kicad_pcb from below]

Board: 4 copper layers, 337.8 x 133.5 mm, 254 parts (78 on the bottom side), 186 nets.

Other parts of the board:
R4: 1500; R_Axial_DIN0204_L3.6mm_D1.6mm_P5.08mm_Horizontal

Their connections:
+5V: R4.2; also elsewhere on the board
unnamed 83: R4.1; also elsewhere on the board

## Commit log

2020-12-19 Add LED lights
2020-12-19 Add ws2812b footprint
2020-12-19 Add LEDs under each key
2020-12-20 Update landing pattern of Cherry MX
2020-12-26 Add 3d models
2020-12-26 Add more tracks for LEDs
2020-12-27 More tracks...
2020-12-28 Finish routing tracks
2020-12-28 Add negative of the copper layers
2020-12-28 Add mounting holes; move some tracks
2020-12-28 Update negative copper PDF
2020-12-29 Move PCB references
2020-12-29 Add printable PDFs
2020-12-31 Improve GND stiching
2021-01-16 Change a mounting hole
2021-01-16 Add pullup resistor to D-
2021-03-20 Remove prints directory
2021-03-20 Move undiscipline library to keyboard-parts
2021-03-20 Move undiscipline project to its own dir
2021-03-20 Add undiscipline without leds
2021-03-20 Add editorconfig
2021-03-20 Add USBaspLoader with patch
2021-03-20 Add script to parse KLE
2021-03-20 Update gitignore
2021-03-21 Redesign the whole noled layout
2021-03-22 Update uv mask
2021-03-26 Add plate drawing
2021-04-18 Add plates
